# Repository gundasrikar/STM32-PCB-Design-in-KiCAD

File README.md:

# STM32 Schematic and PCB Design

# STM32 Schematic Design

The **STM32F103C8** is a microcontroller from the STM32F1 series by STMicroelectronics. Here are some key features:
**Core:** ARM 32-bit Cortex-M3 CPU running at up to 72 MHz.
**Memory:** 64 KB of Flash memory and 20 KB of SRAM.
**Peripherals:** Includes USB, CAN, multiple timers, ADCs, and communication interfaces like SPI, I2C, and USART.
**Power Supply:** Operates from 2.0 to 3.6 V.
**I/Os:** Up to 80 fast I/O ports.

# STM32 Layout Design KiCad View

# STM32 Layout Design

# STM32 3D PCB

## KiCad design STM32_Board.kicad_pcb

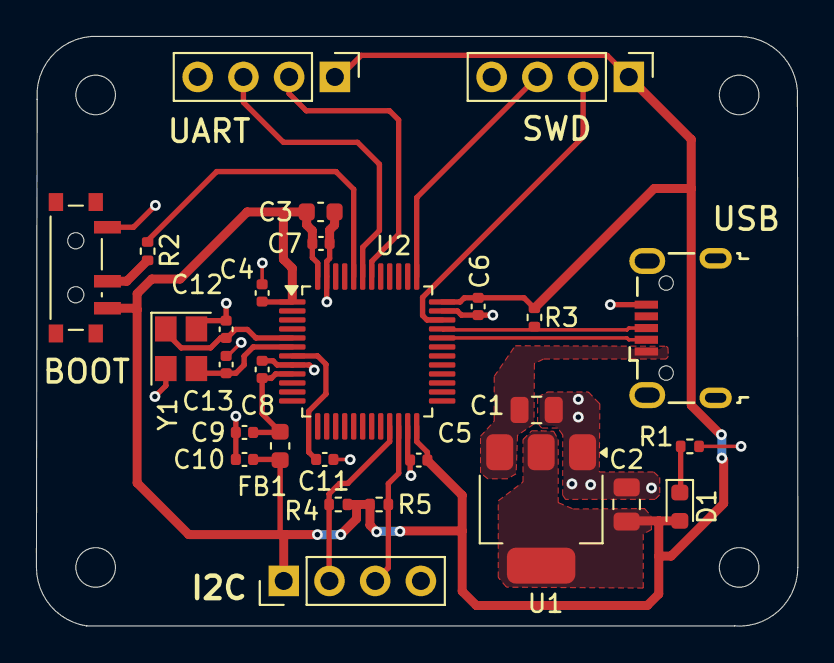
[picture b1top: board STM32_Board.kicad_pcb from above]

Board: 2 copper layers, 42.3 x 32.8 mm, 32 parts (0 on the bottom side), 18 nets.

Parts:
C1, C2: 22u; C_0805_2012Metric
C3: 10u; C_0603_1608Metric
C4, C5, C6, C7, C11: 100n; C_0402_1005Metric
C8: 10n; C_0402_1005Metric
C9, C10: 1u; C_0402_1005Metric
C12, C13: 10p; C_0402_1005Metric
D1: RED LED; LED_0603_1608Metric
FB1: 120R; L_0603_1608Metric
H1, H2, H3, H4: MountingHole; MountingHole_2.2mm_M2
J1: USB_B_Micro; USB_Micro-B_Wuerth_629105150521
J2, J3, J4: Conn_01x04_Pin; PinHeader_1x04_P2.54mm_Vertical
R1, R4, R5: 1.5k; R_0402_1005Metric
R2: 10k; R_0402_1005Metric
R3: 1k5; R_0402_1005Metric
SW1: SW_SPDT; SW_SPDT_PCM12
U1: AMS1117-3.3; SOT-223-3_TabPin2
U2: STM32F103C8Tx; LQFP-48_7x7mm_P0.5mm
Y1: 16MHz; Crystal_SMD_3225-4Pin_3.2x2.5mm

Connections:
+3.3VCC: C2.1, C3.1, C4.1, C5.1, C6.1, C7.1, C10.1, D1.2 (A), FB1.2, J2.1, J3.1, J4.1, R3.1, R4.2, R5.2, SW1.3 (C), U1.2 (VO), U2.1 (VBAT), U2.24 (VDD), U2.36 (VDD), U2.48 (VDD)
+3.3VCCAnalog: C8.1, C9.1, FB1.1, U2.9 (VDDA)
/BOOTO: R2.2, U2.44 (BOOT0)
/I2C2_SCL: J4.2, R4.1, U2.21 (PB10)
/I2C2_SDA: J4.3, R5.1, U2.22 (PB11)
/NRST: C11.1, U2.7 (NRST)
/OSCIN: C12.1, U2.5 (PD0), Y1.1
/OSCOUT: C13.1, U2.6 (PD1), Y1.3
/PWR_LED_K: D1.1 (K), R1.2
/SWCLK: J3.3, U2.37 (PA14)
/SWDIO: J3.2, U2.34 (PA13)
/SW_BOOTO: R2.1, SW1.2 (B)
/USART1_RX: J2.3, U2.43 (PB7)
/USART1_TX: J2.2, U2.42 (PB6)
/USB_D+: J1.3 (D+), R3.2, U2.33 (PA12)
/USB_D-: J1.2 (D-), U2.32 (PA11)
GND: C1.2, C2.2, C3.2, C4.2, C5.2, C6.2, C7.2, C8.2, C9.2, C10.2, C11.2, C12.2, C13.2, J1.5 (GND), J2.4, J3.4, J4.4, R1.1, SW1.1 (A), U1.1 (GND), U2.8 (VSSA), U2.23 (VSS), U2.35 (VSS), U2.47 (VSS), Y1.2, Y1.4
VBUS: C1.1, J1.1 (VBUS), U1.3 (VI)

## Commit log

2025-01-29 README.md
